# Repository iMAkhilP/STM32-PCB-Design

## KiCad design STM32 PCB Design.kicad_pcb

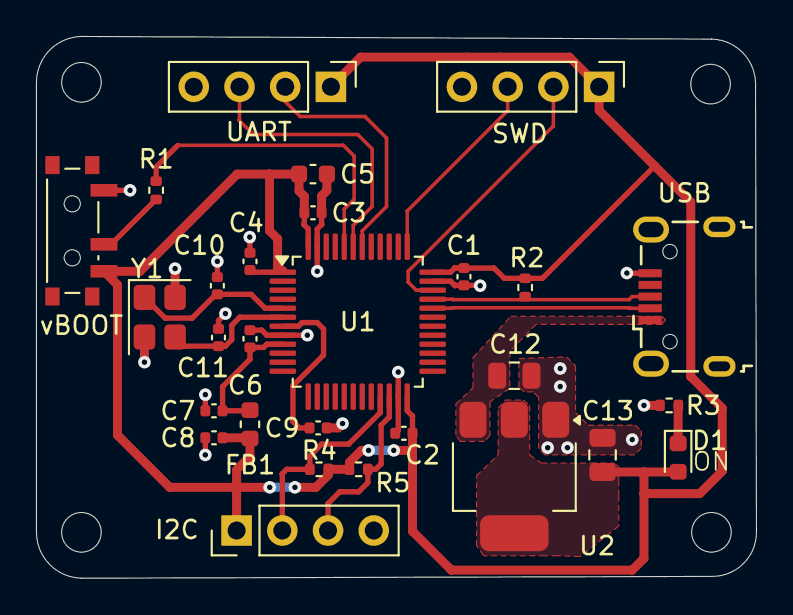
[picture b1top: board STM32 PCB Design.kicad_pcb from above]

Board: 2 copper layers, 40.0 x 30.1 mm, 32 parts (0 on the bottom side), 18 nets.

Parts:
C1, C2, C3, C4, C9: 100n; C_0402_1005Metric
C5: 10u; C_0603_1608Metric
C6: 10n; C_0402_1005Metric
C7, C8: 1u; C_0402_1005Metric
C10, C11: 10p; C_0402_1005Metric
C12, C13: 22u; C_0805_2012Metric
D1: RED; LED_0603_1608Metric
FB1: 120R; L_0603_1608Metric
H1, H2, H3, H4: MountingHole; MountingHole_2.2mm_M2
I2C: Conn_01x04_Pin; PinHeader_1x04_P2.54mm_Vertical
R1: 10k; R_0402_1005Metric
R2, R3, R4, R5: 1k5; R_0402_1005Metric
SWD: Conn_01x04_Pin; PinHeader_1x04_P2.54mm_Vertical
U1: STM32F103C8T6; LQFP-48_7x7mm_P0.5mm
U2: AMS1117-3.3; SOT-223-3_TabPin2
UART: Conn_01x04_Pin; PinHeader_1x04_P2.54mm_Vertical
USB: USB_B_Micro; USB_Micro-B_Wuerth_629105150521
Y1: 16MHz; Crystal_SMD_3225-4Pin_3.2x2.5mm
vBOOT: SW_SPDT; SW_SPDT_PCM12

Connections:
+3.3V: C1.1, C2.1, C3.1, C4.1, C5.1, C8.1, C13.1, D1.2 (A), FB1.2, I2C.1, R2.1, R4.2, R5.2, SWD.1, U1.1 (VBAT), U1.24 (VDD), U1.36 (VDD), U1.48 (VDD), U2.2 (VO), UART.1, vBOOT.3 (C)
+3.3VA: C6.1, C7.1, FB1.1, U1.9 (VDDA)
/BOOT0: R1.2, U1.44 (BOOT0)
/HSE_IN: C10.1, U1.5 (PD0), Y1.1
/HSE_OUT: C11.1, U1.6 (PD1), Y1.3
/I2C2_SCL: I2C.2, R4.1, U1.21 (PB10)
/I2C2_SDA: I2C.3, R5.1, U1.22 (PB11)
/NRST: C9.1, U1.7 (NRST)
/PWR_LED_K: D1.1 (K), R3.2
/SWCLK: SWD.3, U1.37 (PA14)
/SWDIO: SWD.2, U1.34 (PA13)
/SW_BOOT0: R1.1, vBOOT.2 (B)
/USART1_RX: U1.43 (PB7), UART.3
/USART1_TX: U1.42 (PB6), UART.2
/USB_D+: R2.2, U1.33 (PA12), USB.3 (D+)
/USB_D-: U1.32 (PA11), USB.2 (D-)
GND: C1.2, C2.2, C3.2, C4.2, C5.2, C6.2, C7.2, C8.2, C9.2, C10.2, C11.2, C12.2, C13.2, I2C.4, R3.1, SWD.4, U1.8 (VSSA), U1.23 (VSS), U1.35 (VSS), U1.47 (VSS), U2.1 (GND), UART.4, USB.5 (GND), Y1.2, Y1.4, vBOOT.1 (A)
VBUS: C12.1, U2.3 (VI), USB.1 (VBUS)

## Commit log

2025-05-20 Create STM32 PCB Design
